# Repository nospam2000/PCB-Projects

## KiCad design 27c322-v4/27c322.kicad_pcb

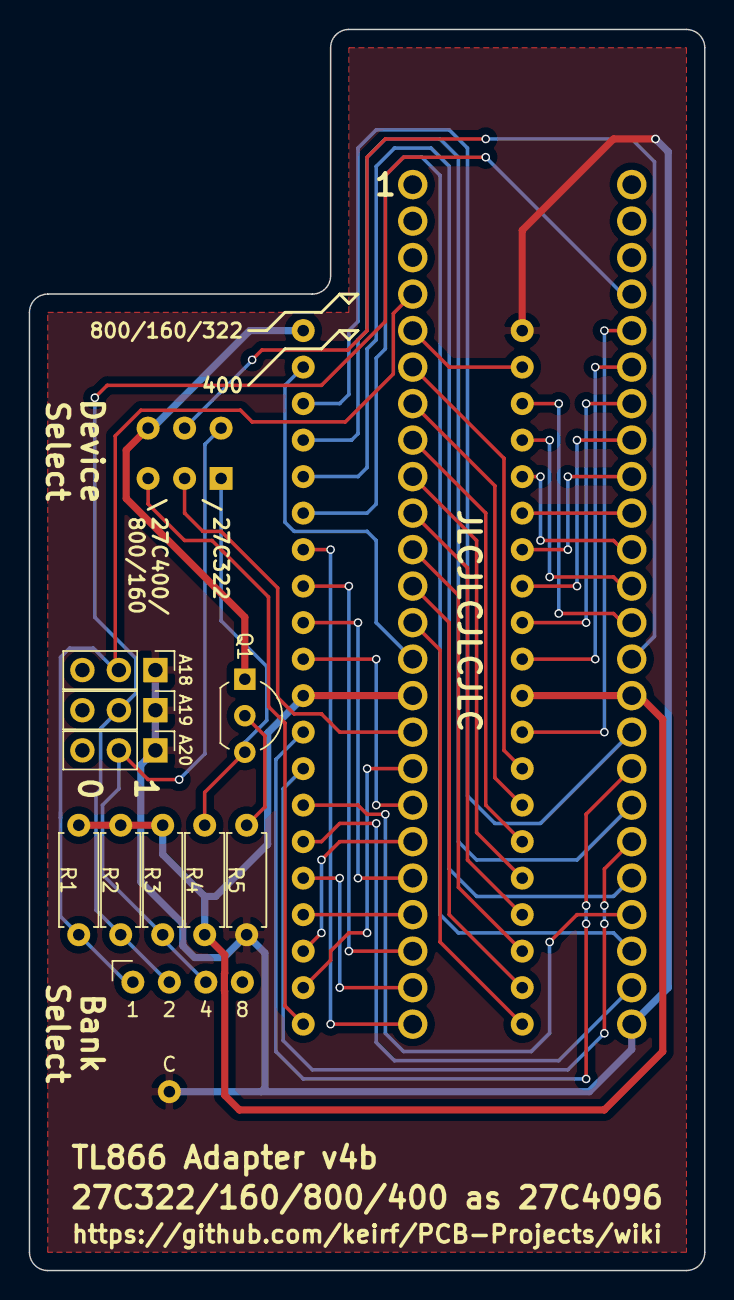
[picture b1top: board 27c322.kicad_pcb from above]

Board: 2 copper layers, 47.0 x 86.4 mm, 13 parts (0 on the bottom side), 46 nets.

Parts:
A18, A19, A20: Jumper_3_Open; PinHeader_1x03_P2.54mm_Vertical
Q1: 2N3906TAR; TO-92L_Inline_Wide
R1, R2, R3, R4: 10K; R_Axial_DIN0207_L6.3mm_D2.5mm_P7.62mm_Horizontal
R5: 1K; R_Axial_DIN0207_L6.3mm_D2.5mm_P7.62mm_Horizontal
SW1: Switch_SPDT_x2; DPDT_Slide
SW2: SW_Coded_SH-7010; Rotary_Switch
U1: 27C4096
U2: 27C322; 27C160

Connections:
/A18: A18.2, R1.2, SW2.1, U2.4
/A19: A19.2, R2.2, SW2.2, U2.45
/A20: A20.2, R3.2, SW1.4, SW2.4
/P2: U1.2, U2.14
/P3: U1.3, U2.33
/P4: U1.4, U2.31
/P5: U1.5, U2.29
/P6: U1.6, U2.27
/P7: U1.7, U2.24
/P8: U1.8, U2.22
/P9: U1.9, U2.20
/P10: U1.10, U2.18
/P12: U1.12, U2.32
/P13: U1.13, U2.30
/P14: U1.14, U2.28
/P15: U1.15, U2.26
/P16: U1.16, U2.23
/P17: U1.17, U2.21
/P18: U1.18, U2.19
/P19: U1.19, U2.17
/P20: SW1.3, U1.20
/P21: U1.21, U2.13
/P22: U1.22, U2.12
/P23: U1.23, U2.11
/P24: U1.24, U2.10
/P25: U1.25, U2.9
/P26: U1.26, U2.8
/P27: U1.27, U2.7
/P28: U1.28, U2.6
/P29: U1.29, U2.44
/P31: U1.31, U2.43
/P32: U1.32, U2.42
/P33: U1.33, U2.41
/P34: U1.34, U2.40
/P35: U1.35, U2.39
/P36: U1.36, U2.38
/P37: U1.37, U2.37
/P38: U1.38, U2.36
/P39: U1.39, U2.5
/VCC: A18.1, A19.1, A20.1, R5.2, SW2.C, U1.40, U2.25
/VPP: Q1.1, SW1.6, U1.1
/VSS: R1.1, R2.1, R3.1, R4.2, U1.11, U1.30, U2.15, U2.34
unnamed: Q1.2, R5.1
unnamed: Q1.3, R4.1, SW1.1
unnamed: SW1.2, U2.16
unnamed: SW1.5, U2.35

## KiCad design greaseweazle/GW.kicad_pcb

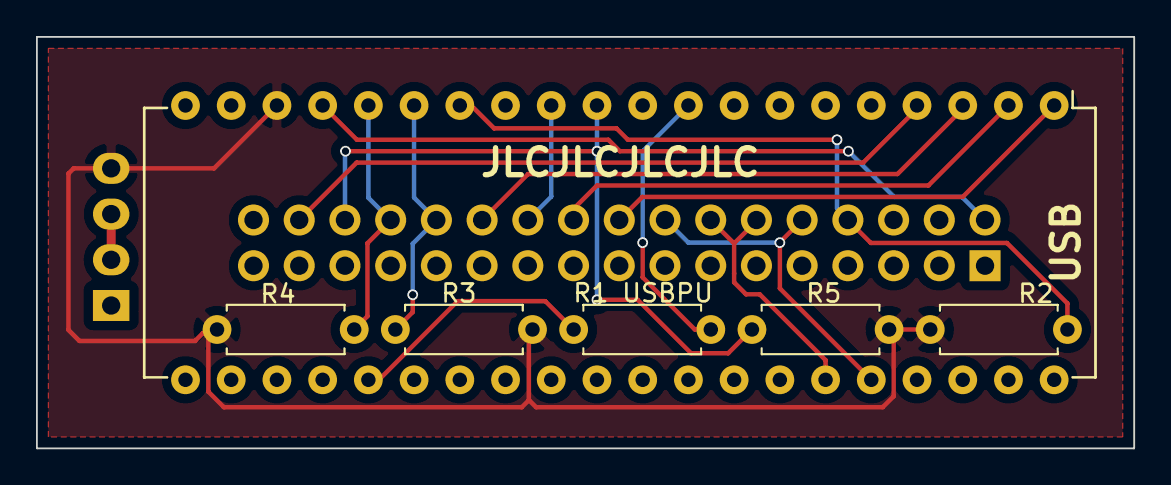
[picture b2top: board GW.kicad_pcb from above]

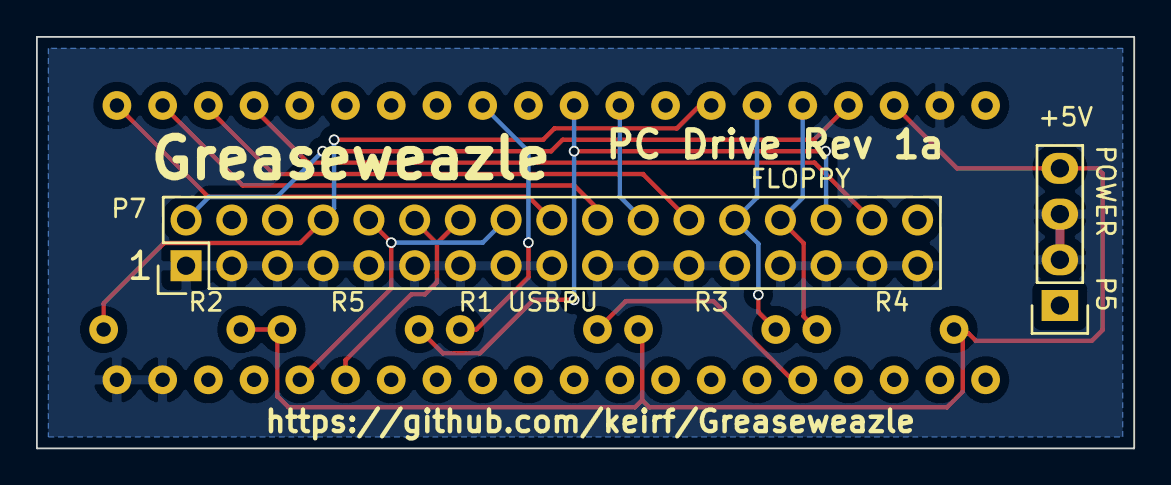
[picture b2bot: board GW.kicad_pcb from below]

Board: 2 copper layers, 61.0 x 22.9 mm, 8 parts (2 on the bottom side), 16 nets.

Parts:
P5: POWER; Pin_Header_Straight_1x04
P7: FLOPPY; Pin_Header_Straight_2x17
R1 USBPU: 1.5K; R_Axial_DIN0207_L6.3mm_D2.5mm_P7.62mm_Horizontal
R2, R3, R4, R5: 1K; R_Axial_DIN0207_L6.3mm_D2.5mm_P7.62mm_Horizontal
U1: TAOBAO; DIP-40_W15.24mm

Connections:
+5V: P5.4, R2.1, R3.1, R4.1, R5.1, U1.18
/USB_CONN: R1 USBPU.1, U1.25
/USB_DP: R1 USBPU.2, U1.9
/_DENSEL: P7.2, U1.17
/_DIR: P7.18, U1.1
/_DKRD: P7.30, R5.2, U1.11
/_DKWD: P7.22, U1.12
/_DKWE: P7.24, U1.3
/_INDEX: P7.8, R2.2, U1.14
/_MTR: P7.10, P7.16, U1.36
/_SEL: P7.12, P7.14, U1.35
/_SIDE: P7.32, U1.4
/_STEP: P7.20, U1.2
/_TRK0: P7.26, R3.2, U1.15
/_WRPROT: P7.28, R4.2, U1.16
GND: P5.2, P5.3, P7.1, P7.3, P7.5, P7.7, P7.9, P7.11, P7.13, P7.15, P7.17, P7.19, P7.21, P7.23, P7.25, P7.27, P7.29, P7.31, P7.33, U1.19, U1.39, U1.40

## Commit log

2021-01-24 made a THT version for easier soldering
2021-01-24 moved SilkScreen on backside away from THT resistors
2021-01-24 added SilkScreen for resistors on back side added "usbpu" to resistor R1
2021-01-24 changed to THT components added jumpers additionally to rotary switch
2021-01-24 moved Q1 and R1 to R5 silk added JLCPCB tag
